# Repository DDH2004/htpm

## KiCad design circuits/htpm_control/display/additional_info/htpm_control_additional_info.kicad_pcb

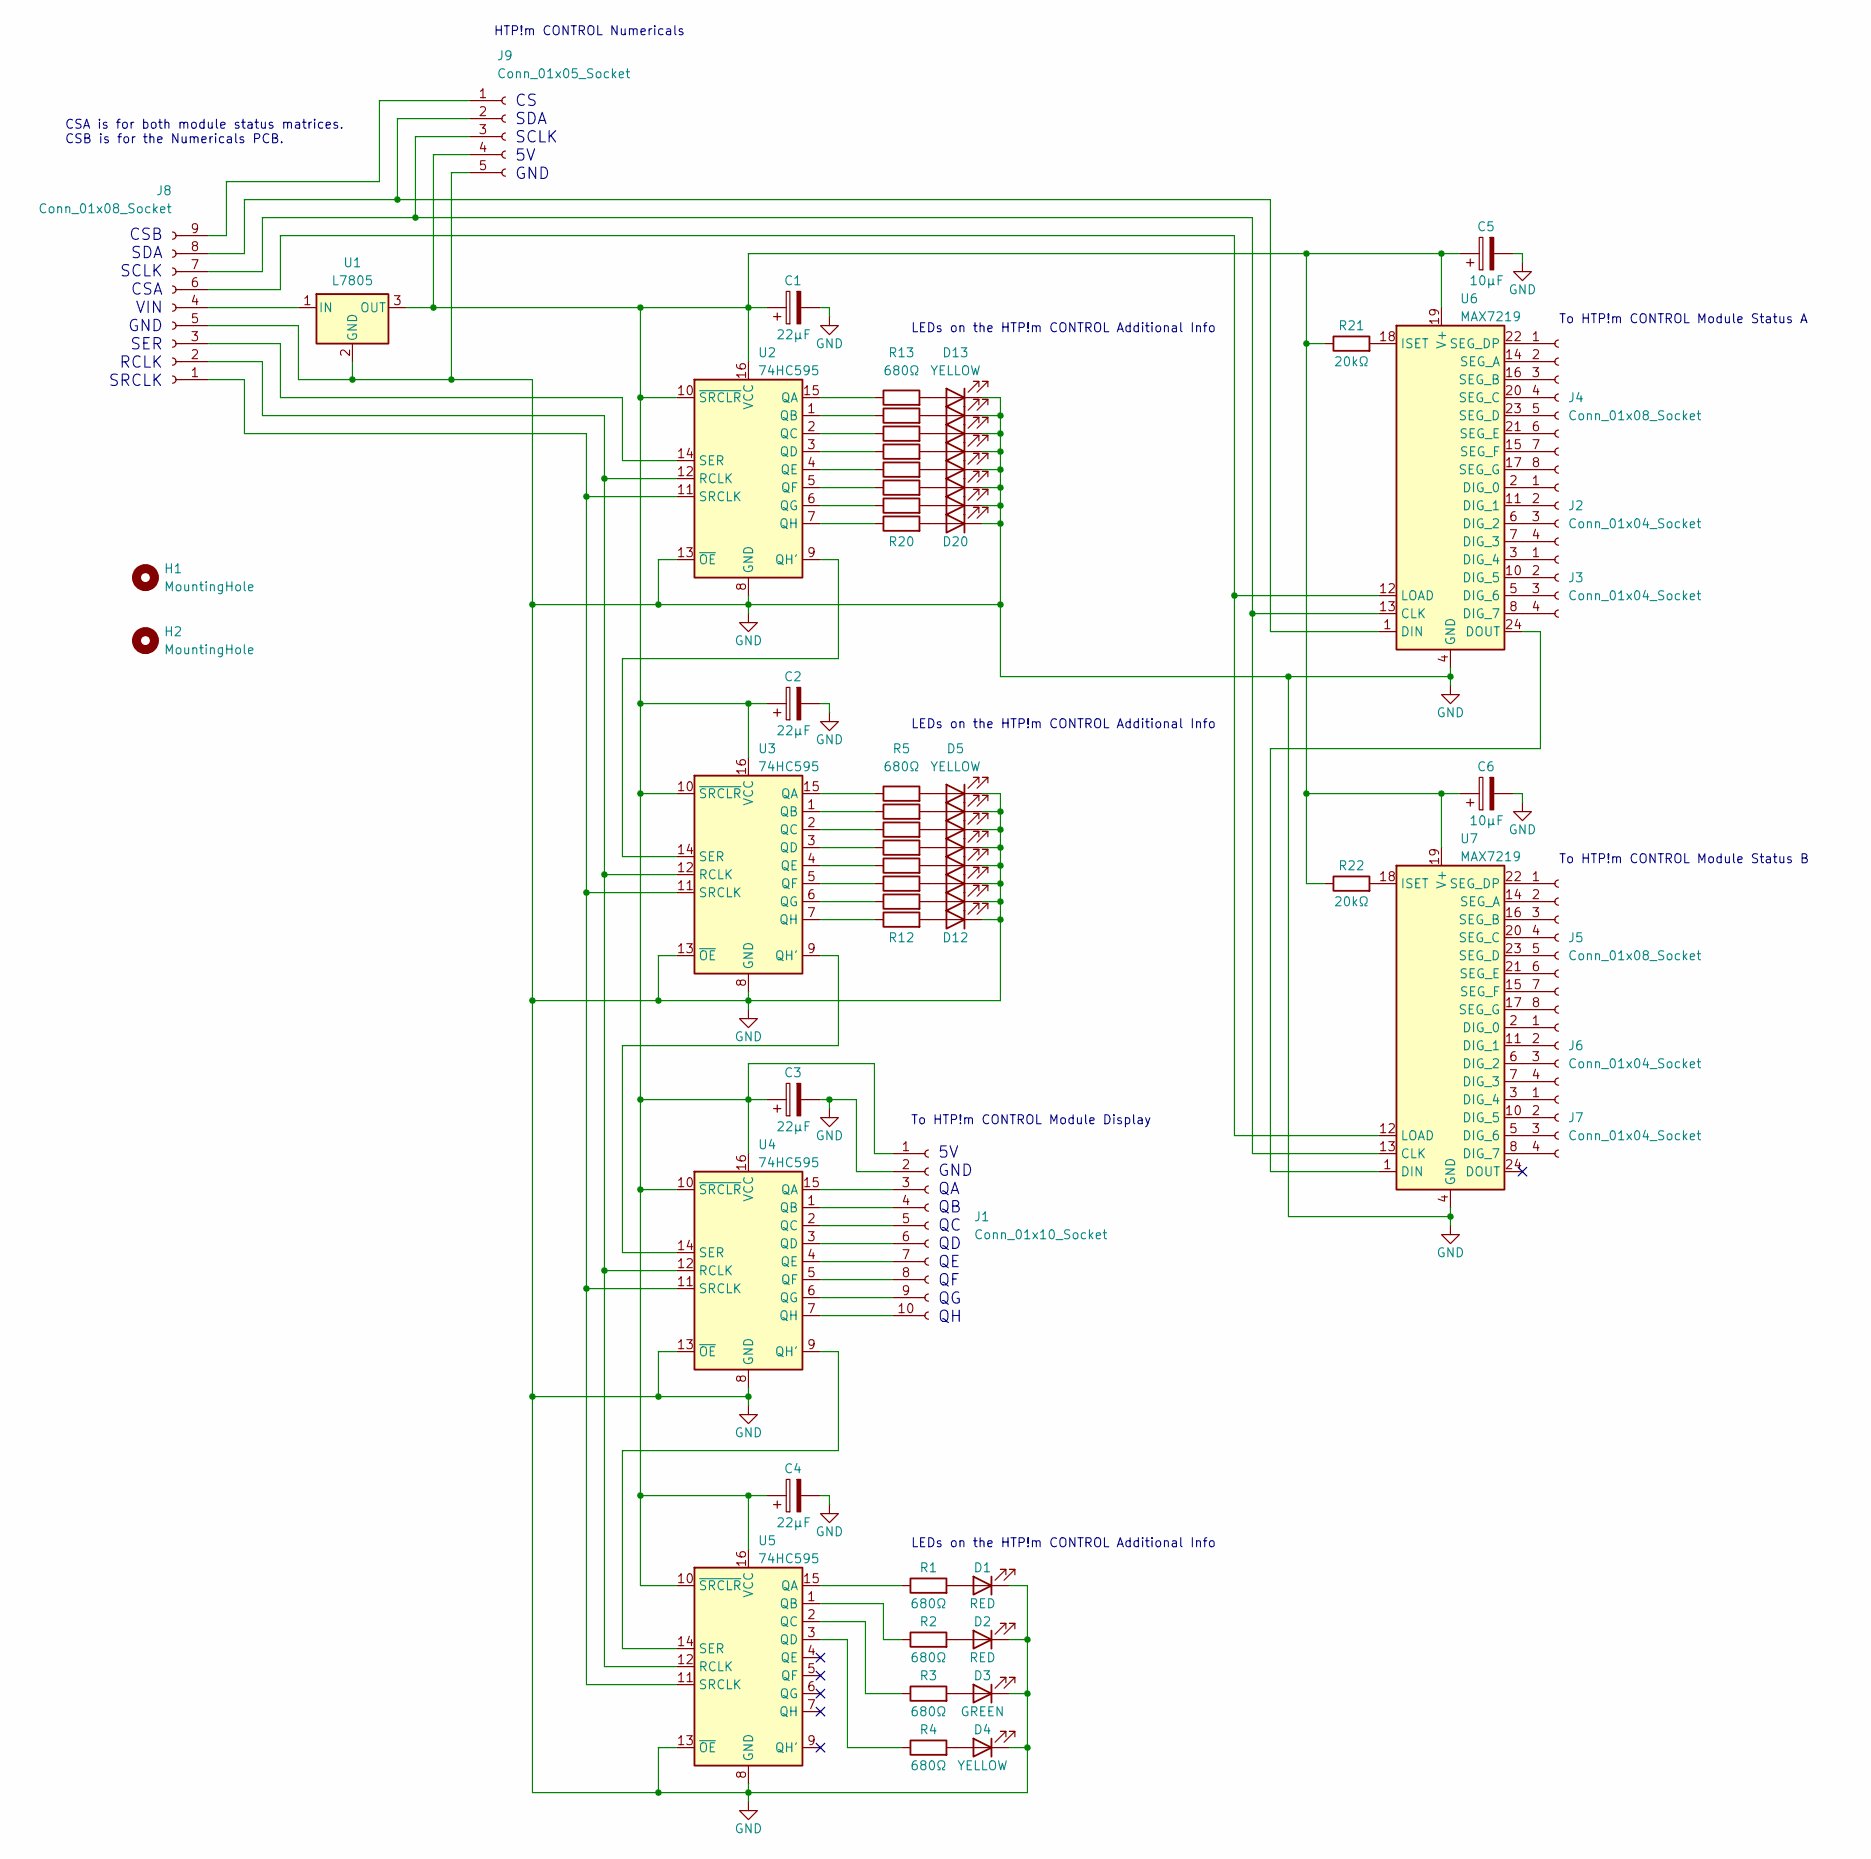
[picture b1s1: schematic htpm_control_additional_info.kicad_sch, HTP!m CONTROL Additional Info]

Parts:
C1, C2, C3, C4: 22μF; CP_Radial_D4.0mm_P2.00mm
C5, C6: 10μF; CP_Radial_D4.0mm_P2.00mm
D1, D2: RED; LED_D5.0mm
D3: GREEN; LED_D5.0mm
D4, D5, D6, D7, D8, D9, D10, D11, D12, D13, D14, D15, D16, D17, D18, D19, D20: YELLOW; LED_D5.0mm
H1, H2: MountingHole; MountingHole_2.5mm
J1: Conn_01x10_Socket; PinHeader_1x10_P2.00mm_Vertical
J2, J3, J6, J7: Conn_01x04_Socket; PinHeader_1x04_P2.00mm_Vertical
J4, J5: Conn_01x08_Socket; PinHeader_1x08_P2.00mm_Vertical
J8: Conn_01x08_Socket; PinHeader_1x09_P2.00mm_Vertical
J9: Conn_01x05_Socket; PinHeader_1x05_P2.00mm_Vertical
R1, R2, R3, R4, R5, R6, R7, R8, R9, R10, R11, R12, R13, R14, R15, R16, R17, R18, R19, R20: 680Ω; R_Axial_DIN0204_L3.6mm_D1.6mm_P7.62mm_Horizontal
R21, R22: 20kΩ; R_Axial_DIN0204_L3.6mm_D1.6mm_P7.62mm_Horizontal
U1: L7805; TO-220-3_Horizontal_TabDown
U2, U3, U4, U5: 74HC595; DIP-16_W7.62mm_Socket
U6, U7: MAX7219; DIP-24_W7.62mm_Socket

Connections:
GND: C1.2, C2.2, C3.2, C4.2, C5.2, C6.2, D1.1 (K), D2.1 (K), D3.1 (K), D4.1 (K), D5.1 (K), D6.1 (K), D7.1 (K), D8.1 (K), D9.1 (K), D10.1 (K), D11.1 (K), D12.1 (K), D13.1 (K), D14.1 (K), D15.1 (K), D16.1 (K), D17.1 (K), D18.1 (K), D19.1 (K), D20.1 (K), J1.2, J8.5, J9.5, U1.2 (GND), U2.8 (GND), U2.13 (~OE), U3.8 (GND), U3.13 (~OE), U4.8 (GND), U4.13 (~OE), U5.8 (GND), U5.13 (~OE), U6.4 (GND), U6.9 (GND), U7.4 (GND), U7.9 (GND)
unnamed: D1.2 (A), R1.2
unnamed: D2.2 (A), R2.2
unnamed: D3.2 (A), R3.2
unnamed: D4.2 (A), R4.2
unnamed: D5.2 (A), R5.2
unnamed: D6.2 (A), R6.2
unnamed: D7.2 (A), R7.2
unnamed: D8.2 (A), R8.2
unnamed: D9.2 (A), R9.2
unnamed: D10.2 (A), R10.2
unnamed: D11.2 (A), R11.2
unnamed: D12.2 (A), R12.2
unnamed: D13.2 (A), R13.2
unnamed: D14.2 (A), R14.2
unnamed: D15.2 (A), R15.2
unnamed: D16.2 (A), R16.2
unnamed: D17.2 (A), R17.2
unnamed: D18.2 (A), R18.2
unnamed: D19.2 (A), R19.2
unnamed: D20.2 (A), R20.2
unnamed: C1.1, C2.1, C3.1, C4.1, C5.1, C6.1, J1.1, J9.4, R21.1, R22.1, U1.3 (OUT), U2.10 (~SRCLR), U2.16 (VCC), U3.10 (~SRCLR), U3.16 (VCC), U4.10 (~SRCLR), U4.16 (VCC), U5.10 (~SRCLR), U5.16 (VCC), U6.19 (V+), U7.19 (V+)
unnamed: J1.3, U4.15 (QA)
unnamed: J1.4, U4.1 (QB)
unnamed: J1.5, U4.2 (QC)
unnamed: J1.6, U4.3 (QD)
unnamed: J1.7, U4.4 (QE)
unnamed: J1.8, U4.5 (QF)
unnamed: J1.9, U4.6 (QG)
unnamed: J1.10, U4.7 (QH)
unnamed: J2.1, U6.2 (DIG_0)
unnamed: J2.2, U6.11 (DIG_1)
unnamed: J2.3, U6.6 (DIG_2)
unnamed: J2.4, U6.7 (DIG_3)
unnamed: J3.1, U6.3 (DIG_4)
unnamed: J3.2, U6.10 (DIG_5)
unnamed: J3.3, U6.5 (DIG_6)
unnamed: J3.4, U6.8 (DIG_7)
unnamed: J4.1, U6.22 (SEG_DP)
unnamed: J4.2, U6.14 (SEG_A)
unnamed: J4.3, U6.16 (SEG_B)
unnamed: J4.4, U6.20 (SEG_C)
unnamed: J4.5, U6.23 (SEG_D)
unnamed: J4.6, U6.21 (SEG_E)
unnamed: J4.7, U6.15 (SEG_F)
unnamed: J4.8, U6.17 (SEG_G)
unnamed: J5.1, U7.22 (SEG_DP)
unnamed: J5.2, U7.14 (SEG_A)
unnamed: J5.3, U7.16 (SEG_B)
unnamed: J5.4, U7.20 (SEG_C)
unnamed: J5.5, U7.23 (SEG_D)
unnamed: J5.6, U7.21 (SEG_E)
unnamed: J5.7, U7.15 (SEG_F)
unnamed: J5.8, U7.17 (SEG_G)
unnamed: J6.1, U7.2 (DIG_0)
unnamed: J6.2, U7.11 (DIG_1)
unnamed: J6.3, U7.6 (DIG_2)
unnamed: J6.4, U7.7 (DIG_3)
unnamed: J7.1, U7.3 (DIG_4)
unnamed: J7.2, U7.10 (DIG_5)
unnamed: J7.3, U7.5 (DIG_6)
unnamed: J7.4, U7.8 (DIG_7)
unnamed: J8.1, U2.11 (SRCLK), U3.11 (SRCLK), U4.11 (SRCLK), U5.11 (SRCLK)
unnamed: J8.2, U2.12 (RCLK), U3.12 (RCLK), U4.12 (RCLK), U5.12 (RCLK)
unnamed: J8.3, U2.14 (SER)
unnamed: J8.4, U1.1 (IN)
unnamed: J8.6, U6.12 (LOAD), U7.12 (LOAD)
unnamed: J8.7, J9.3, U6.13 (CLK), U7.13 (CLK)
unnamed: J8.8, J9.2, U6.1 (DIN)
unnamed: J8.9, J9.1
unnamed: R13.1, U2.15 (QA)
unnamed: R14.1, U2.1 (QB)
unnamed: R15.1, U2.2 (QC)
unnamed: R16.1, U2.3 (QD)
unnamed: R17.1, U2.4 (QE)
unnamed: R18.1, U2.5 (QF)
unnamed: R19.1, U2.6 (QG)
unnamed: U2.9 (QH'), U3.14 (SER)
unnamed: R20.1, U2.7 (QH)
unnamed: R5.1, U3.15 (QA)
unnamed: R6.1, U3.1 (QB)
unnamed: R7.1, U3.2 (QC)
unnamed: R8.1, U3.3 (QD)
unnamed: R9.1, U3.4 (QE)
unnamed: R10.1, U3.5 (QF)
unnamed: R11.1, U3.6 (QG)
unnamed: U3.9 (QH'), U4.14 (SER)
unnamed: R12.1, U3.7 (QH)
unnamed: U4.9 (QH'), U5.14 (SER)
unnamed: R1.1, U5.15 (QA)
unnamed: R2.1, U5.1 (QB)
unnamed: R3.1, U5.2 (QC)
unnamed: R4.1, U5.3 (QD)
unnamed: U6.24 (DOUT), U7.1 (DIN)
unnamed: R21.2, U6.18 (ISET)
unnamed: R22.2, U7.18 (ISET)

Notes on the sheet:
LEDs on the HTP!m CONTROL Additional Info
To HTP!m CONTROL Module Display
CS SDA SCLK 5V GND
To HTP!m CONTROL Module Status A
CSA is for both module status matrices. CSB is for the Numericals PCB.
HTP!m CONTROL Numericals
5V GND QA QB QC QD QE QF QG QH
CSB SDA SCLK CSA VIN GND SER RCLK SRCLK
To HTP!m CONTROL Module Status B

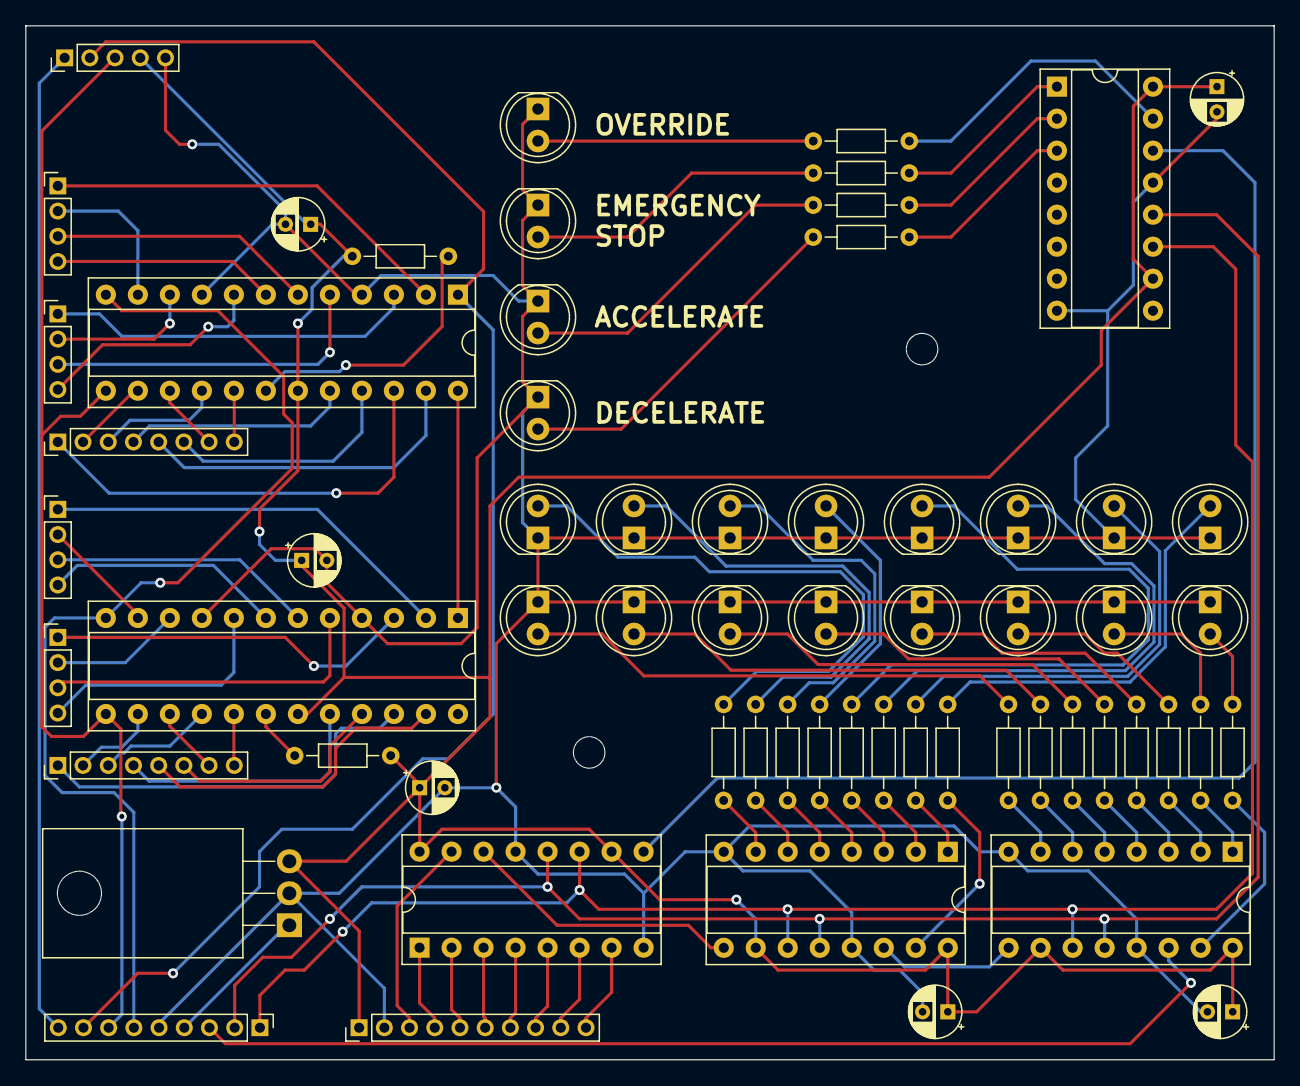
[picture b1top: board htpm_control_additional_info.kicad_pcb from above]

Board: 2 copper layers, 99.1 x 82.0 mm, 66 parts (0 on the bottom side), 96 nets.

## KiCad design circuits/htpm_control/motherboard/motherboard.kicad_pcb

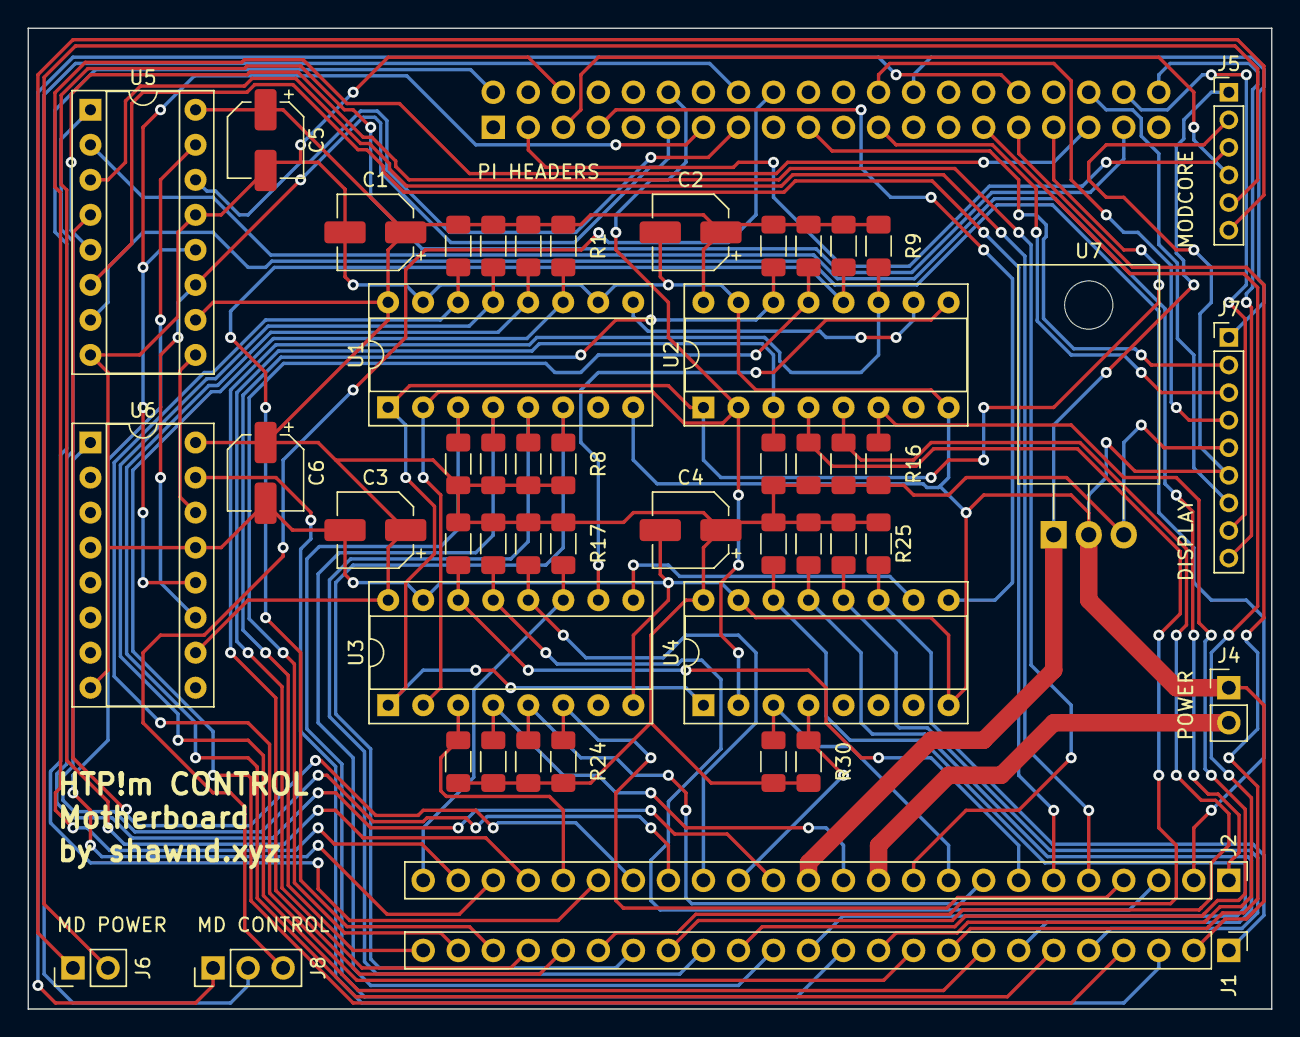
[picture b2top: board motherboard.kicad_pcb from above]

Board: 2 copper layers, 90.2 x 71.1 mm, 51 parts (1 on the bottom side), 73 nets.

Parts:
C1, C2, C3, C4, C5, C6: 22μF; CP_Elec_5x5.4
J1, J2: PinHeader_1x24_P2.54mm_Vertical
J3: Conn_01x40_Socket; PinSocket_2x20_P2.54mm_Vertical
J4: PinHeader_1x02_P2.54mm_Vertical
J5: Connector_Modcore; PinHeader_1x06_P2.00mm_Vertical
J6: Motor_Power; PinHeader_1x02_P2.54mm_Vertical
J7: Connector_Display; PinHeader_1x09_P2.00mm_Vertical
J8: Connector_Motor_Driver; PinHeader_1x03_P2.54mm_Vertical
R1, R2, R3, R4, R5, R6, R7, R8, R9, R10, R11, R12, R13, R14, R15, R16, R17, R18, R19, R20, R21, R22, R23, R24, R25, R26, R27, R28, R29, R30: 4.7kΩ; R_1206_3216Metric_Pad1.30x1.75mm_HandSolder
U1, U2, U3, U4: 74HC165; DIP-16_W7.62mm_Socket
U5, U6: 74HC595; DIP-16_W7.62mm_Socket
U7: L7805; TO-220-3_Horizontal_TabDown

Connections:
GND: C1.2, C2.2, C3.2, C4.2, C5.2, C6.2, J1.2 (GND), J3.6 (GND), J4.1 (GND), J5.2 (GND), J7.6 (GND), U1.8 (GND), U1.10 (DS), U1.15 (~CE), U2.8 (GND), U2.15 (~CE), U3.8 (GND), U3.15 (~CE), U4.8 (GND), U4.15 (~CE), U5.8 (GND), U5.13 (~OE), U6.8 (GND), U6.13 (~OE), U7.2 (GND)
unnamed: J1.4 (BIT_0), R1.2, U1.11 (D0)
unnamed: J1.6 (BIT_1), R2.2, U1.12 (D1)
unnamed: J1.8 (BIT_2), R3.2, U1.13 (D2)
unnamed: J1.10 (BIT_3), R4.2, U1.14 (D3)
unnamed: J1.12 (BIT_4), R5.2, U1.3 (D4)
unnamed: J1.14 (BIT_5), R6.2, U1.4 (D5)
unnamed: J1.16 (BIT_6), R7.2, U1.5 (D6)
unnamed: J1.18 (BIT_7), R8.2, U1.6 (D7)
unnamed: J1.20 (BIT_8), R9.2, U2.11 (D0)
unnamed: J1.22 (BIT_9), R10.2, U2.12 (D1)
unnamed: J1.23 (BIT_A), R11.2, U2.13 (D2)
unnamed: J1.24 (BIT_B), R12.2, U2.14 (D3)
unnamed: J1.21 (BIT_C), R13.2, U2.3 (D4)
unnamed: J1.19 (BIT_D), R14.2, U2.4 (D5)
unnamed: J1.17 (BIT_E), R15.2, U2.5 (D6)
unnamed: J1.15 (BIT_F), R16.2, U2.6 (D7)
unnamed: J1.13 (FWD/BWD_SWITCH), R28.2, U4.14 (D3)
unnamed: J1.7 (MODULE_OVERRIDE_SWITCH), R27.2, U4.13 (D2)
unnamed: J1.3 (PUSH_LED), U6.15 (QA)
unnamed: J1.5 (PUSH_SWITCH), R26.2, U4.12 (D1)
unnamed: J1.1 (RAIL_OVERRIDE_SWITCH), R25.2, U4.11 (D0)
unnamed: J1.11 (VELOCITY_CLK), J3.29 (GPIO5)
unnamed: J1.9 (VELOCITY_DT), J3.31 (GPIO6)
unnamed: J2.22 (00_LED), U5.15 (QA)
unnamed: J2.24 (00_SWITCH), R17.2, U3.11 (D0)
unnamed: J2.14 (01_LED), U5.1 (QB)
unnamed: J2.16 (01_SWITCH), R18.2, U3.12 (D1)
unnamed: J2.1 (02_LED), U5.2 (QC)
unnamed: J2.3 (02_SWITCH), R19.2, U3.13 (D2)
unnamed: J2.5 (03_LED), U5.3 (QD)
unnamed: J2.7 (03_SWITCH), R20.2, U3.14 (D3)
unnamed: J2.19 (5V), J3.2 (5v)
unnamed: J2.18 (10_LED), U5.4 (QE)
unnamed: J2.20 (10_SWITCH), R21.2, U3.3 (D4)
unnamed: J2.10 (11_LED), U5.5 (QF)
unnamed: J2.12 (11_SWITCH), R22.2, U3.4 (D5)
unnamed: J2.6 (12_LED), U5.6 (QG)
unnamed: J2.8 (12_SWITCH), R23.2, U3.5 (D6)
unnamed: J2.2 (13_LED), U5.7 (QH)
unnamed: J2.4 (13_SWITCH), R24.2, U3.6 (D7)
unnamed: J2.17 (EMERGENCY_STOP_LED), U6.1 (QB)
unnamed: J2.15 (EMERGENCY_STOP_SWITCH), R30.2, U4.4 (D5)
unnamed: J2.11 (POWER_A), J4.2 (12V)
unnamed: J2.13 (POWER_B), J5.1 (12V), U7.1 (IN)
unnamed: J2.9 (TIME_ACTIVE_SWITCH), R29.2, U4.3 (D4)
unnamed: J2.23 (TIME_SET_CLK), J3.35 (GPIO19(PCM_FS))
unnamed: J2.21 (TIME_SET_DT), J3.37 (GPIO26)
unnamed: J3.3 (GPIO2(I2C1_SDA)), J5.3 (I2C_SDA)
unnamed: J3.5 (GPIO3(I2C1_SCL)), J5.4 (I2C_SCLK)
unnamed: J3.7 (GPIO4(GPCLK0)), U4.9 (Q7)
unnamed: J3.26 (GPIO7(SPI0_CE1)), J7.1 (CSB)
unnamed: J3.24 (GPIO8(SPI0_CE0)), J7.4 (CSA)
unnamed: J3.19 (GPIO10(SPI0_MOSI)), J7.2 (SDA)
unnamed: J3.23 (GPIO11(SPI0_SCLK)), J7.3 (SCLK)
unnamed: J3.32 (GPIO12(PWM0)), J8.1 (ENA)
unnamed: J3.33 (GPIO13(PWM1)), U1.1 (~PL), U2.1 (~PL), U3.1 (~PL), U4.1 (~PL)
unnamed: J3.36 (GPIO16), J7.7 (SER)
unnamed: J3.11 (GPIO17), U5.11 (SRCLK), U6.11 (SRCLK)
unnamed: J3.12 (GPIO18(PCM_CLK)), U1.2 (CP), U2.2 (CP), U3.2 (CP), U4.2 (CP)
unnamed: J3.38 (GPIO20(PCM_DIN)), J7.8 (RCLK)
unnamed: J3.40 (GPIO21(PCM_DOUT)), J7.9 (SRCLK)
unnamed: J3.15 (GPIO22), U5.14 (SER)
unnamed: J3.16 (GPIO23), J8.2 (IN1)
unnamed: J3.18 (GPIO24), J8.3 (IN2)
unnamed: J3.13 (GPIO27), U5.12 (RCLK), U6.12 (RCLK)
unnamed: J5.6 (VA), J6.1 (VA)
unnamed: J5.5 (VB), J6.2 (VB)
unnamed: C1.1, C2.1, C3.1, C4.1, C5.1, C6.1, J7.5 (5V), R1.1, R2.1, R3.1, R4.1, R5.1, R6.1, R7.1, R8.1, R9.1, R10.1, R11.1, R12.1, R13.1, R14.1, R15.1, R16.1, R17.1, R18.1, R19.1, R20.1, R21.1, R22.1, R23.1, R24.1, R25.1, R26.1, R27.1, R28.1, R29.1, R30.1, U1.16 (VCC), U2.16 (VCC), U3.16 (VCC), U4.16 (VCC), U5.10 (~SRCLR), U5.16 (VCC), U6.10 (~SRCLR), U6.16 (VCC), U7.3 (OUT)
unnamed: U1.9 (Q7), U2.10 (DS)
unnamed: U2.9 (Q7), U3.10 (DS)
unnamed: U3.9 (Q7), U4.10 (DS)
unnamed: U5.9 (QH'), U6.14 (SER)

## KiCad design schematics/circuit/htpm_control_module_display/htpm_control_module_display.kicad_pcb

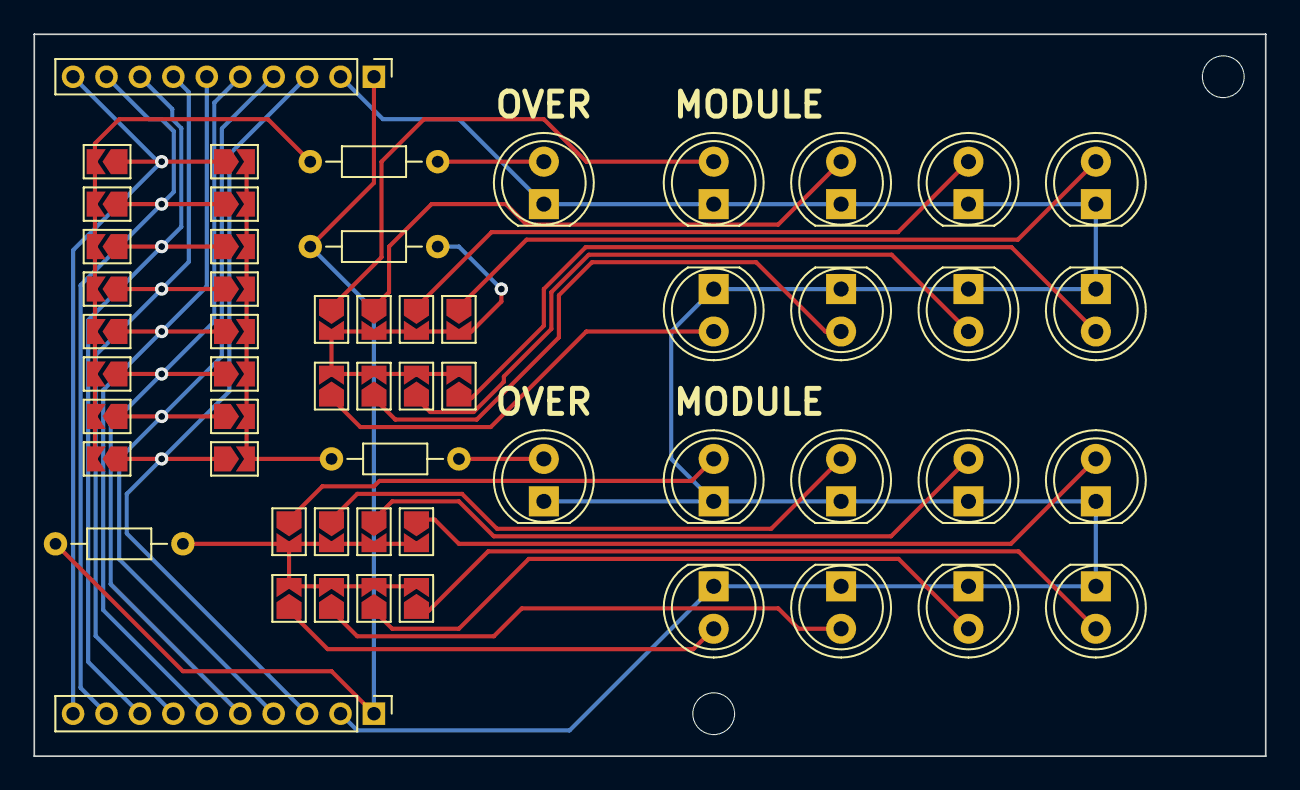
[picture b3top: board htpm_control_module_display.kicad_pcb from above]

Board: 2 copper layers, 73.7 x 43.2 mm, 58 parts (0 on the bottom side), 33 nets.

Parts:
D1, D2: RED; LED_D5.0mm
D3, D4, D5, D6, D7, D8, D9, D10, D11, D12, D13, D14, D15, D16, D17, D18: BLUE; LED_D5.0mm
H1, H2: MountingHole; MountingHole_2.5mm
J1, J2: Conn_01x10_Socket; PinHeader_1x10_P2.00mm_Vertical
JP1, JP2, JP3, JP4, JP5, JP6, JP7, JP8, JP9, JP10, JP11, JP12, JP13, JP14, JP15, JP16, JP17, JP18, JP19, JP20, JP21, JP22, JP23, JP24, JP25, JP26, JP27, JP28, JP29, JP30, JP31, JP32: SolderJumper_2_Bridged; SolderJumper-2_P1.3mm_Open_TrianglePad1.0x1.5mm
R1, R2, R3, R4: 10kΩ; R_Axial_DIN0204_L3.6mm_D1.6mm_P7.62mm_Horizontal

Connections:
+3.3V: R3.1, R4.1
+5V: J1.5V (Pin_1), J2.5v (Pin_1)
GND: D1.1 (K), D2.1 (K), D3.1 (K), D4.1 (K), D5.1 (K), D6.1 (K), D7.1 (K), D8.1 (K), D9.1 (K), D10.1 (K), D11.1 (K), D12.1 (K), D13.1 (K), D14.1 (K), D15.1 (K), D16.1 (K), D17.1 (K), D18.1 (K), J1.GND (Pin_2), J2.GND (Pin_2)
unnamed: D1.2 (A), R1.2
unnamed: D2.2 (A), R2.2
unnamed: D3.2 (A), JP1.1 (A)
unnamed: D4.2 (A), JP2.1 (A)
unnamed: D5.2 (A), JP3.1 (A)
unnamed: D6.2 (A), JP4.1 (A)
unnamed: D7.2 (A), JP5.1 (A)
unnamed: D8.2 (A), JP6.1 (A)
unnamed: D9.2 (A), JP7.1 (A)
unnamed: D10.2 (A), JP8.1 (A)
unnamed: D11.2 (A), JP9.1 (A)
unnamed: D12.2 (A), JP10.1 (A)
unnamed: D13.2 (A), JP11.1 (A)
unnamed: D14.2 (A), JP12.1 (A)
unnamed: D15.2 (A), JP13.1 (A)
unnamed: D16.2 (A), JP14.1 (A)
unnamed: D17.2 (A), JP15.1 (A)
unnamed: D18.2 (A), JP16.1 (A)
unnamed: J1.QA (Pin_3), J2.QA (Pin_3), JP24.1 (A), JP25.1 (A)
unnamed: J1.QB (Pin_4), J2.QB (Pin_4), JP23.1 (A), JP26.1 (A)
unnamed: J1.QC (Pin_5), J2.QC (Pin_5), JP22.1 (A), JP27.1 (A)
unnamed: J1.QD (Pin_6), J2.QD (Pin_6), JP21.1 (A), JP28.1 (A)
unnamed: J1.QE (Pin_7), J2.QE (Pin_7), JP20.1 (A), JP29.1 (A)
unnamed: J1.QF (Pin_8), J2.QF (Pin_8), JP19.1 (A), JP30.1 (A)
unnamed: J1.QG (Pin_9), J2.QG (Pin_9), JP18.1 (A), JP31.1 (A)
unnamed: J1.QH (Pin_10), J2.QH (Pin_10), JP17.1 (A), JP32.1 (A)
unnamed: JP1.2 (B), JP2.2 (B), JP3.2 (B), JP4.2 (B), JP5.2 (B), JP6.2 (B), JP7.2 (B), JP8.2 (B), R4.2
unnamed: JP9.2 (B), JP10.2 (B), JP11.2 (B), JP12.2 (B), JP13.2 (B), JP14.2 (B), JP15.2 (B), JP16.2 (B), R3.2
unnamed: JP17.2 (B), JP18.2 (B), JP19.2 (B), JP20.2 (B), JP21.2 (B), JP22.2 (B), JP23.2 (B), JP24.2 (B), R2.1
unnamed: JP25.2 (B), JP26.2 (B), JP27.2 (B), JP28.2 (B), JP29.2 (B), JP30.2 (B), JP31.2 (B), JP32.2 (B), R1.1

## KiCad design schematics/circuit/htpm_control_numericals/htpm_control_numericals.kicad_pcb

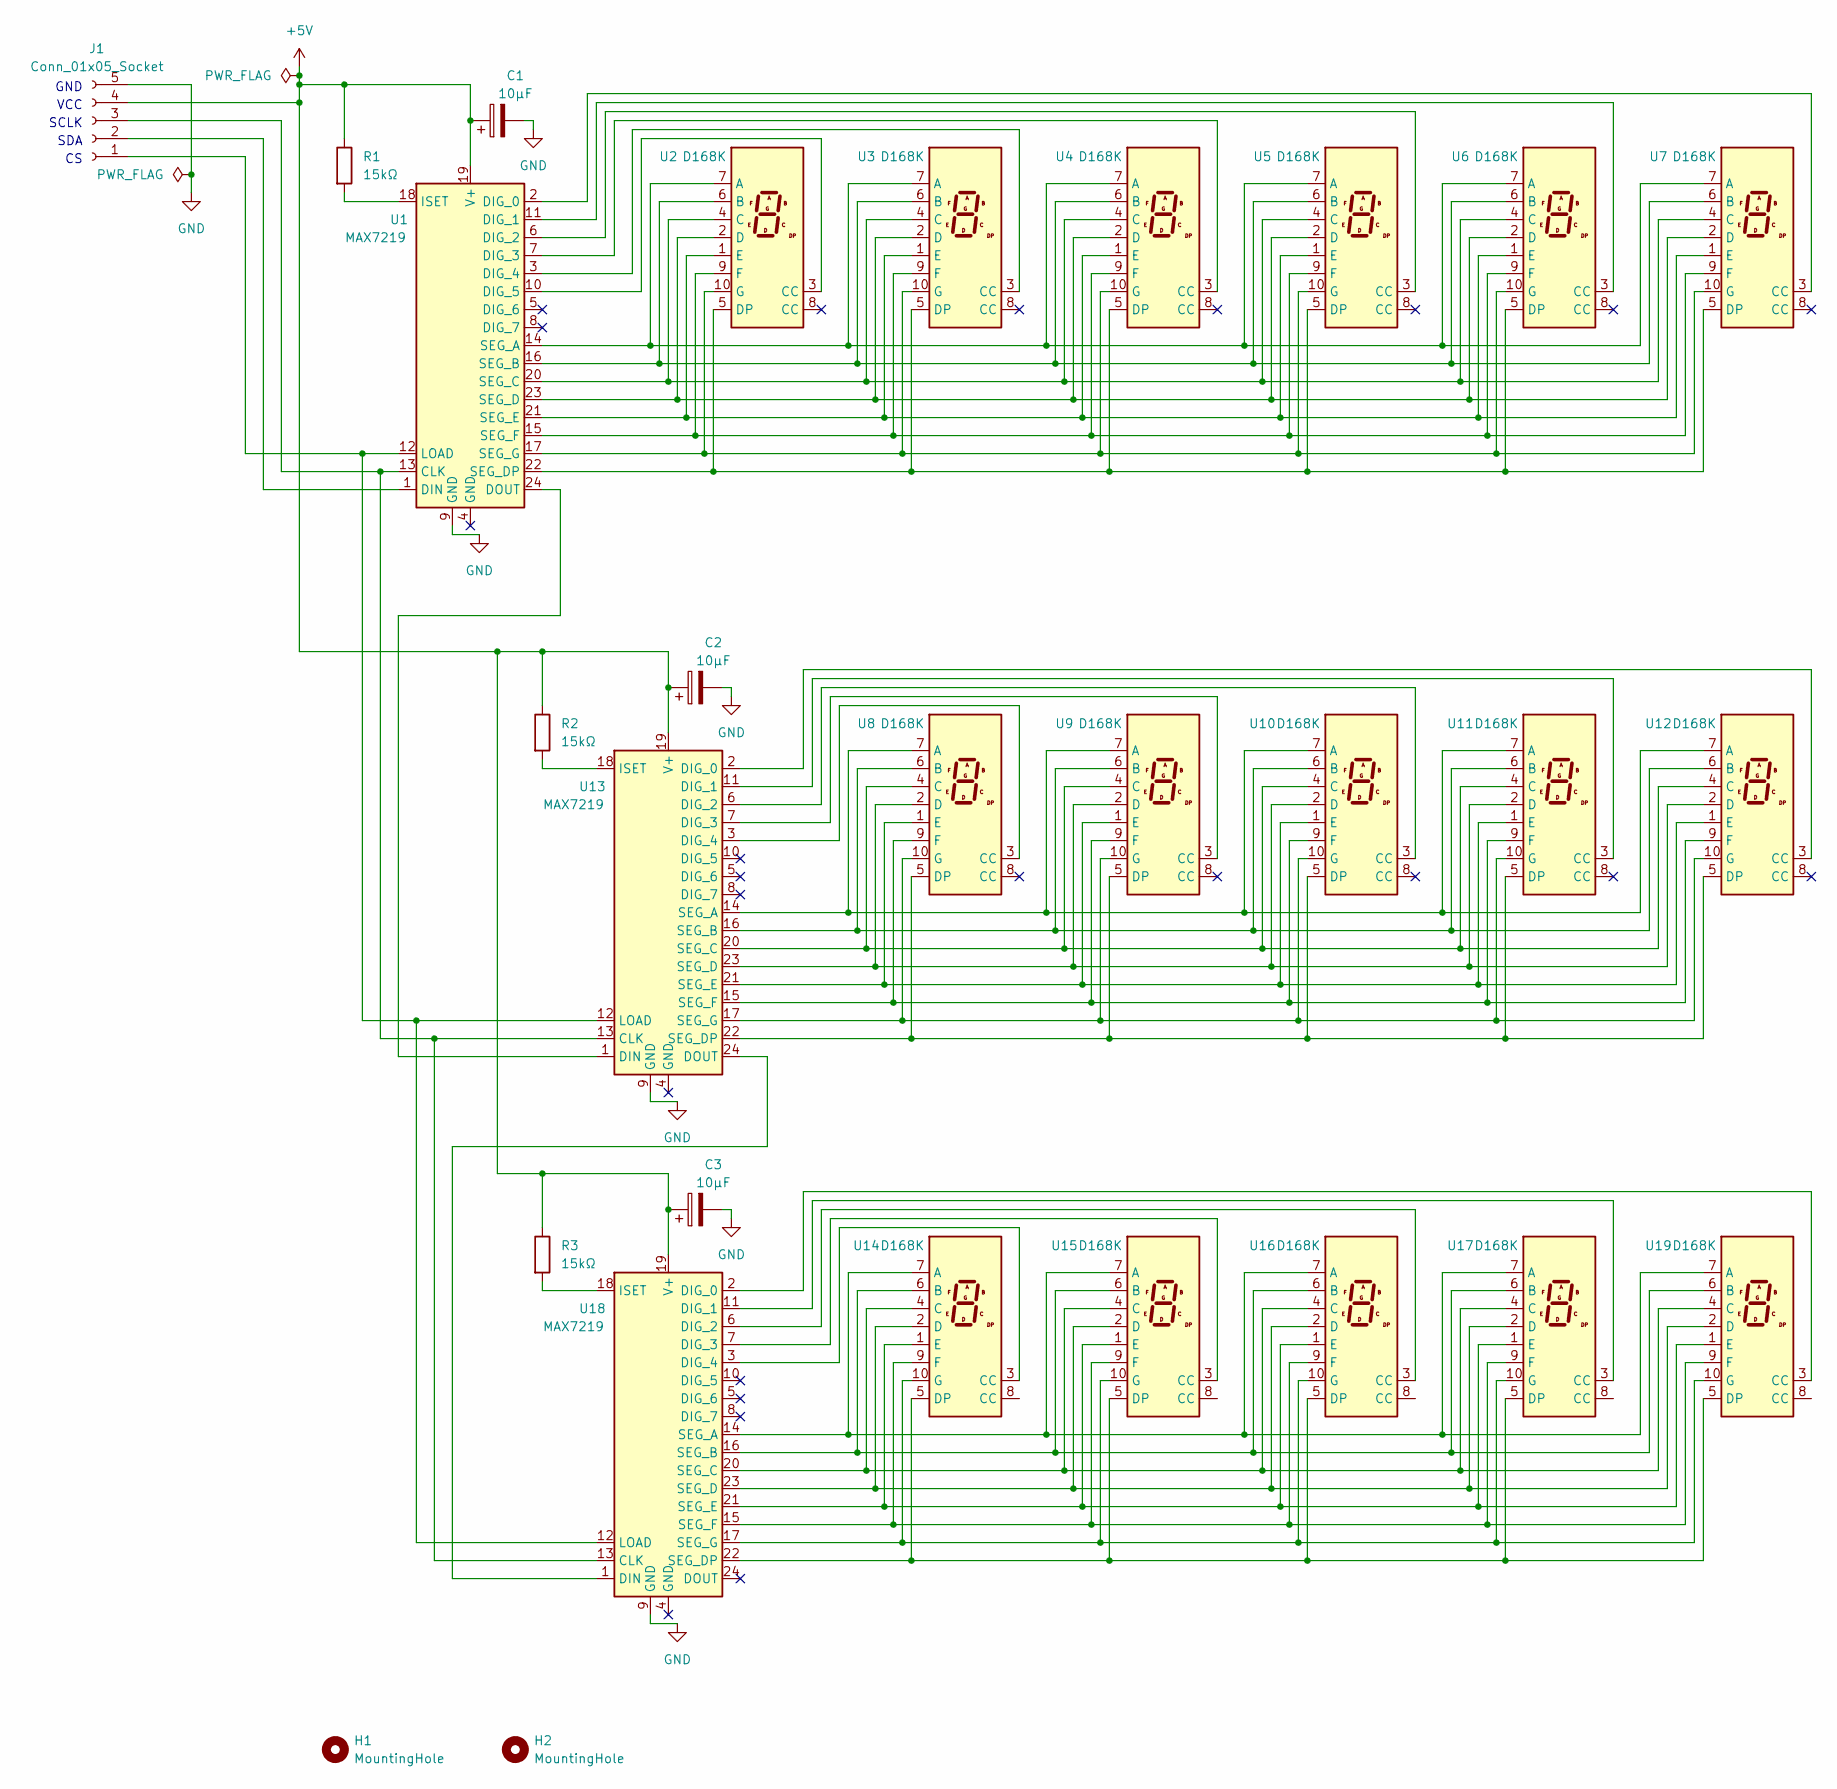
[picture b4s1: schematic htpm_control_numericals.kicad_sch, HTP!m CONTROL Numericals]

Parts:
C1, C2, C3: 10μF; CP_Radial_D4.0mm_P2.00mm
H1, H2: MountingHole; MountingHole_2.5mm
J1: Conn_01x05_Socket; PinHeader_1x05_P2.00mm_Vertical
R1, R2, R3: 15kΩ; R_Axial_DIN0204_L3.6mm_D1.6mm_P7.62mm_Horizontal
U1, U13, U18: MAX7219; DIP-24_W7.62mm_Socket
U2, U3, U4, U5, U6, U7, U8, U9, U10, U11, U12, U14, U15, U16, U17, U19: D168K; D1X8K

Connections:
+5V: C1.1, C2.1, C3.1, J1.4, R1.1, R2.1, R3.1, U1.19 (V+), U13.19 (V+), U18.19 (V+)
GND: C1.2, C2.2, C3.2, J1.5, U1.9 (GND), U13.9 (GND), U18.9 (GND)
unnamed: J1.1, U1.12 (LOAD), U13.12 (LOAD), U18.12 (LOAD)
unnamed: J1.2, U1.1 (DIN)
unnamed: J1.3, U1.13 (CLK), U13.13 (CLK), U18.13 (CLK)
unnamed: U1.2 (DIG_0), U7.3 (CC)
unnamed: U1.11 (DIG_1), U6.3 (CC)
unnamed: U1.6 (DIG_2), U5.3 (CC)
unnamed: U1.7 (DIG_3), U4.3 (CC)
unnamed: U1.3 (DIG_4), U3.3 (CC)
unnamed: U1.10 (DIG_5), U2.3 (CC)
unnamed: U1.24 (DOUT), U13.1 (DIN)
unnamed: R1.2, U1.18 (ISET)
unnamed: U1.14 (SEG_A), U2.7 (A), U3.7 (A), U4.7 (A), U5.7 (A), U6.7 (A), U7.7 (A)
unnamed: U1.16 (SEG_B), U2.6 (B), U3.6 (B), U4.6 (B), U5.6 (B), U6.6 (B), U7.6 (B)
unnamed: U1.20 (SEG_C), U2.4 (C), U3.4 (C), U4.4 (C), U5.4 (C), U6.4 (C), U7.4 (C)
unnamed: U1.23 (SEG_D), U2.2 (D), U3.2 (D), U4.2 (D), U5.2 (D), U6.2 (D), U7.2 (D)
unnamed: U1.22 (SEG_DP), U2.5 (DP), U3.5 (DP), U4.5 (DP), U5.5 (DP), U6.5 (DP), U7.5 (DP)
unnamed: U1.21 (SEG_E), U2.1 (E), U3.1 (E), U4.1 (E), U5.1 (E), U6.1 (E), U7.1 (E)
unnamed: U1.15 (SEG_F), U2.9 (F), U3.9 (F), U4.9 (F), U5.9 (F), U6.9 (F), U7.9 (F)
unnamed: U1.17 (SEG_G), U2.10 (G), U3.10 (G), U4.10 (G), U5.10 (G), U6.10 (G), U7.10 (G)
unnamed: U8.7 (A), U9.7 (A), U10.7 (A), U11.7 (A), U12.7 (A), U13.14 (SEG_A)
unnamed: U8.6 (B), U9.6 (B), U10.6 (B), U11.6 (B), U12.6 (B), U13.16 (SEG_B)
unnamed: U8.4 (C), U9.4 (C), U10.4 (C), U11.4 (C), U12.4 (C), U13.20 (SEG_C)
unnamed: U8.2 (D), U9.2 (D), U10.2 (D), U11.2 (D), U12.2 (D), U13.23 (SEG_D)
unnamed: U8.5 (DP), U9.5 (DP), U10.5 (DP), U11.5 (DP), U12.5 (DP), U13.22 (SEG_DP)
unnamed: U8.1 (E), U9.1 (E), U10.1 (E), U11.1 (E), U12.1 (E), U13.21 (SEG_E)
unnamed: U8.9 (F), U9.9 (F), U10.9 (F), U11.9 (F), U12.9 (F), U13.15 (SEG_F)
unnamed: U8.10 (G), U9.10 (G), U10.10 (G), U11.10 (G), U12.10 (G), U13.17 (SEG_G)
unnamed: U12.3 (CC), U13.2 (DIG_0)
unnamed: U11.3 (CC), U13.11 (DIG_1)
unnamed: U10.3 (CC), U13.6 (DIG_2)
unnamed: U9.3 (CC), U13.7 (DIG_3)
unnamed: U8.3 (CC), U13.3 (DIG_4)
unnamed: U13.24 (DOUT), U18.1 (DIN)
unnamed: R2.2, U13.18 (ISET)
unnamed: U14.7 (A), U15.7 (A), U16.7 (A), U17.7 (A), U18.14 (SEG_A), U19.7 (A)
unnamed: U14.6 (B), U15.6 (B), U16.6 (B), U17.6 (B), U18.16 (SEG_B), U19.6 (B)
unnamed: U14.4 (C), U15.4 (C), U16.4 (C), U17.4 (C), U18.20 (SEG_C), U19.4 (C)
unnamed: U14.2 (D), U15.2 (D), U16.2 (D), U17.2 (D), U18.23 (SEG_D), U19.2 (D)
unnamed: U14.5 (DP), U15.5 (DP), U16.5 (DP), U17.5 (DP), U18.22 (SEG_DP), U19.5 (DP)
unnamed: U14.1 (E), U15.1 (E), U16.1 (E), U17.1 (E), U18.21 (SEG_E), U19.1 (E)
unnamed: U14.9 (F), U15.9 (F), U16.9 (F), U17.9 (F), U18.15 (SEG_F), U19.9 (F)
unnamed: U14.10 (G), U15.10 (G), U16.10 (G), U17.10 (G), U18.17 (SEG_G), U19.10 (G)
unnamed: U18.2 (DIG_0), U19.3 (CC)
unnamed: U17.3 (CC), U18.11 (DIG_1)
unnamed: U16.3 (CC), U18.6 (DIG_2)
unnamed: U15.3 (CC), U18.7 (DIG_3)
unnamed: U14.3 (CC), U18.3 (DIG_4)
unnamed: R3.2, U18.18 (ISET)

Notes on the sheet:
VCC
SDA
SCLK
GND

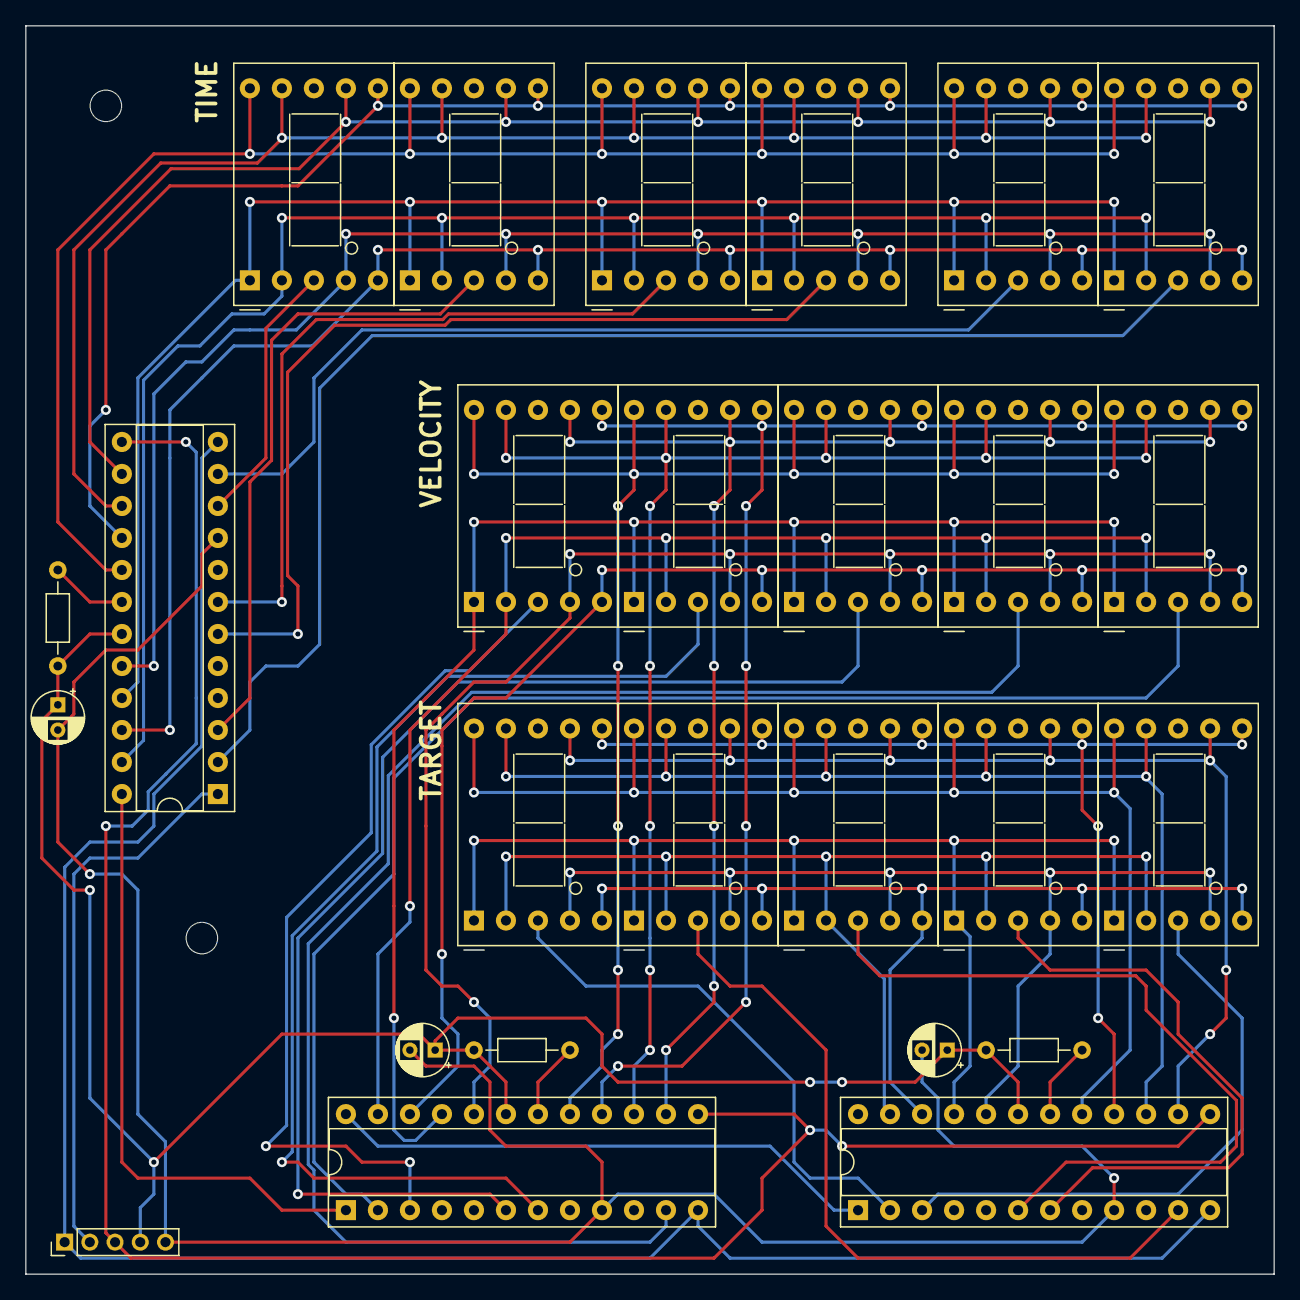
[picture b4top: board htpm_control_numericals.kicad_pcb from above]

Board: 2 copper layers, 99.1 x 99.1 mm, 28 parts (0 on the bottom side), 50 nets.
